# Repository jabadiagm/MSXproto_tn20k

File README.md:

# MSXproto_tn20k
Placa de prototipado para cartucho MSX y Tang Nano 20K

Placa de prototipo para conectar una Tang Nano 20K a una ranura de cartucho MSX. Se incluyen adaptadores de nivel de 5V a 3.3V para los pines de salida digitales del cartucho.

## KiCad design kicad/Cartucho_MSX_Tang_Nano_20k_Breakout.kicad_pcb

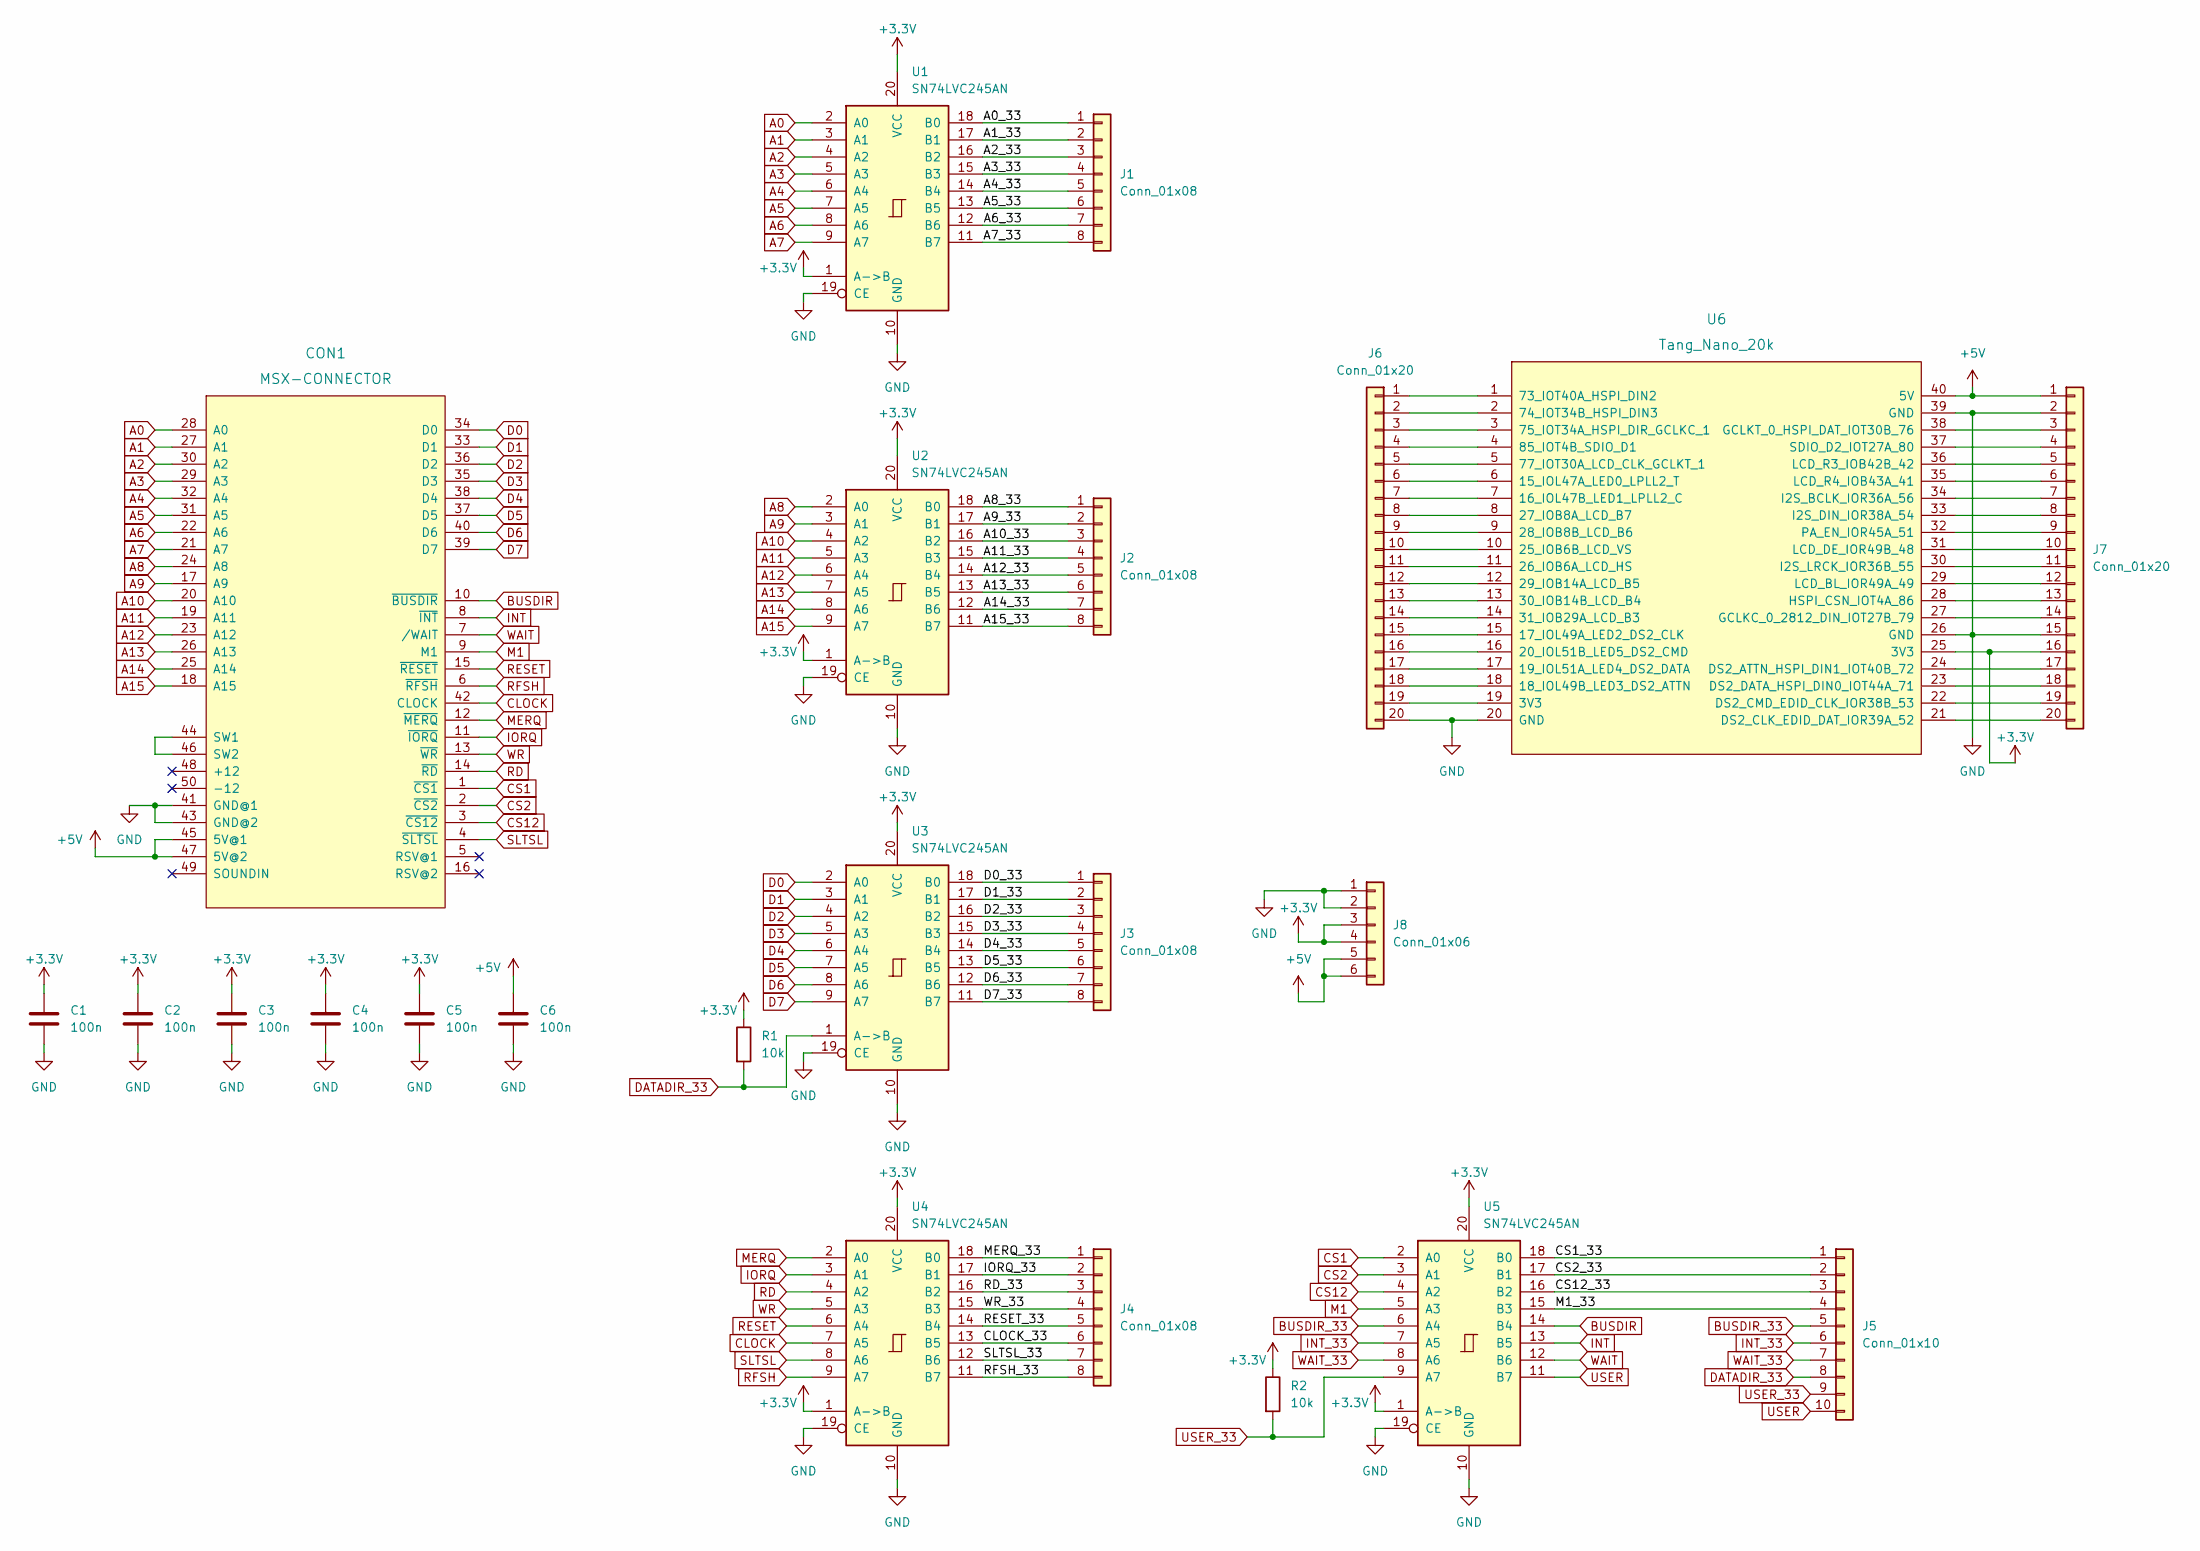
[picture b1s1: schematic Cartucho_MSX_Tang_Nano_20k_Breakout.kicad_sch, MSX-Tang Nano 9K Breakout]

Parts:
C1, C2, C3, C4, C5, C6: 100n; C_Disc_D4.3mm_W1.9mm_P5.00mm
CON1: MSX-CONNECTOR; CARTRIDGE_MSX_XL
J1, J2, J3, J4: Conn_01x08; PinSocket_1x08_P2.54mm_Vertical
J5: Conn_01x10; PinSocket_1x10_P2.54mm_Vertical
J6, J7: Conn_01x20; PinSocket_1x20_P2.54mm_Vertical
J8: Conn_01x06; PinSocket_1x06_P2.54mm_Vertical
R1, R2: 10k; R_Axial_DIN0207_L6.3mm_D2.5mm_P7.62mm_Horizontal
U1, U2, U3, U4, U5: SN74LVC245AN; DIP-20_W7.62mm
U6: Tang_Nano_20k

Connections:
/A0_33: J1.1, U1.18 (B0)
/A1_33: J1.2, U1.17 (B1)
/A2_33: J1.3, U1.16 (B2)
/A3_33: J1.4, U1.15 (B3)
/A4_33: J1.5, U1.14 (B4)
/A5_33: J1.6, U1.13 (B5)
/A6_33: J1.7, U1.12 (B6)
/A7_33: J1.8, U1.11 (B7)
/A8_33: J2.1, U2.18 (B0)
/A9_33: J2.2, U2.17 (B1)
/A10_33: J2.3, U2.16 (B2)
/A11_33: J2.4, U2.15 (B3)
/A12_33: J2.5, U2.14 (B4)
/A13_33: J2.6, U2.13 (B5)
/A14_33: J2.7, U2.12 (B6)
/A15_33: J2.8, U2.11 (B7)
/CLOCK_33: J4.6, U4.13 (B5)
/CS1_33: J5.1, U5.18 (B0)
/CS2_33: J5.2, U5.17 (B1)
/CS12_33: J5.3, U5.16 (B2)
/D0_33: J3.1, U3.18 (B0)
/D1_33: J3.2, U3.17 (B1)
/D2_33: J3.3, U3.16 (B2)
/D3_33: J3.4, U3.15 (B3)
/D4_33: J3.5, U3.14 (B4)
/D5_33: J3.6, U3.13 (B5)
/D6_33: J3.7, U3.12 (B6)
/D7_33: J3.8, U3.11 (B7)
/IORQ_33: J4.2, U4.17 (B1)
/M1_33: J5.4, U5.15 (B3)
/MERQ_33: J4.1, U4.18 (B0)
/RD_33: J4.3, U4.16 (B2)
/RESET_33: J4.5, U4.14 (B4)
/RFSH_33: J4.8, U4.11 (B7)
/SLTSL_33: J4.7, U4.12 (B6)
/WR_33: J4.4, U4.15 (B3)
A0: CON1.28 (A0), U1.2 (A0)
A1: CON1.27 (A1), U1.3 (A1)
A2: CON1.30 (A2), U1.4 (A2)
A3: CON1.29 (A3), U1.5 (A3)
A4: CON1.32 (A4), U1.6 (A4)
A5: CON1.31 (A5), U1.7 (A5)
A6: CON1.22 (A6), U1.8 (A6)
A7: CON1.21 (A7), U1.9 (A7)
A8: CON1.24 (A8), U2.2 (A0)
A9: CON1.17 (A9), U2.3 (A1)
A10: CON1.20 (A10), U2.4 (A2)
A11: CON1.19 (A11), U2.5 (A3)
A12: CON1.23 (A12), U2.6 (A4)
A13: CON1.26 (A13), U2.7 (A5)
A14: CON1.25 (A14), U2.8 (A6)
A15: CON1.18 (A15), U2.9 (A7)
BUSDIR: CON1.10 (~BUSDIR), U5.14 (B4)
BUSDIR_33: J5.5, U5.6 (A4)
CLOCK: CON1.42 (CLOCK), U4.7 (A5)
CS1: CON1.1 (~CS1), U5.2 (A0)
CS2: CON1.2 (~CS2), U5.3 (A1)
CS12: CON1.3 (~CS12), U5.4 (A2)
D0: CON1.34 (D0), U3.2 (A0)
D1: CON1.33 (D1), U3.3 (A1)
D2: CON1.36 (D2), U3.4 (A2)
D3: CON1.35 (D3), U3.5 (A3)
D4: CON1.38 (D4), U3.6 (A4)
D5: CON1.37 (D5), U3.7 (A5)
D6: CON1.40 (D6), U3.8 (A6)
D7: CON1.39 (D7), U3.9 (A7)
DATADIR_33: J5.8, R1.2, U3.1 (A->B)
INT: CON1.8 (~INT), U5.13 (B5)
INT_33: J5.6, U5.7 (A5)
IORQ: CON1.11 (~IORQ), U4.3 (A1)
M1: CON1.9 (M1), U5.5 (A3)
MERQ: CON1.12 (~MERQ), U4.2 (A0)
unnamed: CON1.44 (SW1), CON1.46 (SW2)
unnamed: J6.1, U6.1 (73_IOT40A_HSPI_DIN2)
unnamed: J6.2, U6.2 (74_IOT34B_HSPI_DIN3)
unnamed: J6.3, U6.3 (75_IOT34A_HSPI_DIR_GCLKC_1)
unnamed: J6.4, U6.4 (85_IOT4B_SDIO_D1)
unnamed: J6.5, U6.5 (77_IOT30A_LCD_CLK_GCLKT_1)
unnamed: J6.6, U6.6 (15_IOL47A_LED0_LPLL2_T)
unnamed: J6.7, U6.7 (16_IOL47B_LED1_LPLL2_C)
unnamed: J6.8, U6.8 (27_IOB8A_LCD_B7)
unnamed: J6.9, U6.9 (28_IOB8B_LCD_B6)
unnamed: J6.10, U6.10 (25_IOB6B_LCD_VS)
unnamed: J6.11, U6.11 (26_IOB6A_LCD_HS)
unnamed: J6.12, U6.12 (29_IOB14A_LCD_B5)
unnamed: J6.13, U6.13 (30_IOB14B_LCD_B4)
unnamed: J6.14, U6.14 (31_IOB29A_LCD_B3)
unnamed: J6.15, U6.15 (17_IOL49A_LED2_DS2_CLK)
unnamed: J6.16, U6.16 (20_IOL51B_LED5_DS2_CMD)
unnamed: J6.17, U6.17 (19_IOL51A_LED4_DS2_DATA)
unnamed: J6.18, U6.18 (18_IOL49B_LED3_DS2_ATTN)
unnamed: J6.19, U6.19 (3V3)
unnamed: J7.3, U6.38 (GCLKT_0_HSPI_DAT_IOT30B_76)
unnamed: J7.4, U6.37 (SDIO_D2_IOT27A_80)
unnamed: J7.5, U6.36 (LCD_R3_IOB42B_42)
unnamed: J7.6, U6.35 (LCD_R4_IOB43A_41)
unnamed: J7.7, U6.34 (I2S_BCLK_IOR36A_56)
unnamed: J7.8, U6.33 (I2S_DIN_IOR38A_54)
unnamed: J7.9, U6.32 (PA_EN_IOR45A_51)
unnamed: J7.10, U6.31 (LCD_DE_IOR49B_48)
unnamed: J7.11, U6.30 (I2S_LRCK_IOR36B_55)
unnamed: J7.12, U6.29 (LCD_BL_IOR49A_49)
unnamed: J7.13, U6.28 (HSPI_CSN_IOT4A_86)
unnamed: J7.14, U6.27 (GCLKC_0_2812_DIN_IOT27B_79)
unnamed: J7.17, U6.24 (DS2_ATTN_HSPI_DIN1_IOT40B_72)
unnamed: J7.18, U6.23 (DS2_DATA_HSPI_DIN0_IOT44A_71)
unnamed: J7.19, U6.22 (DS2_CMD_EDID_CLK_IOR38B_53)
unnamed: J7.20, U6.21 (DS2_CLK_EDID_DAT_IOR39A_52)
RD: CON1.14 (~RD), U4.4 (A2)
RESET: CON1.15 (~RESET), U4.6 (A4)
RFSH: CON1.6 (~RFSH), U4.9 (A7)
SLTSL: CON1.4 (~SLTSL), U4.8 (A6)
USER: J5.10, U5.11 (B7)
USER_33: J5.9, R2.2, U5.9 (A7)
WAIT: CON1.7 (/WAIT), U5.12 (B6)
WAIT_33: J5.7, U5.8 (A6)
WR: CON1.13 (~WR), U4.5 (A3)

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
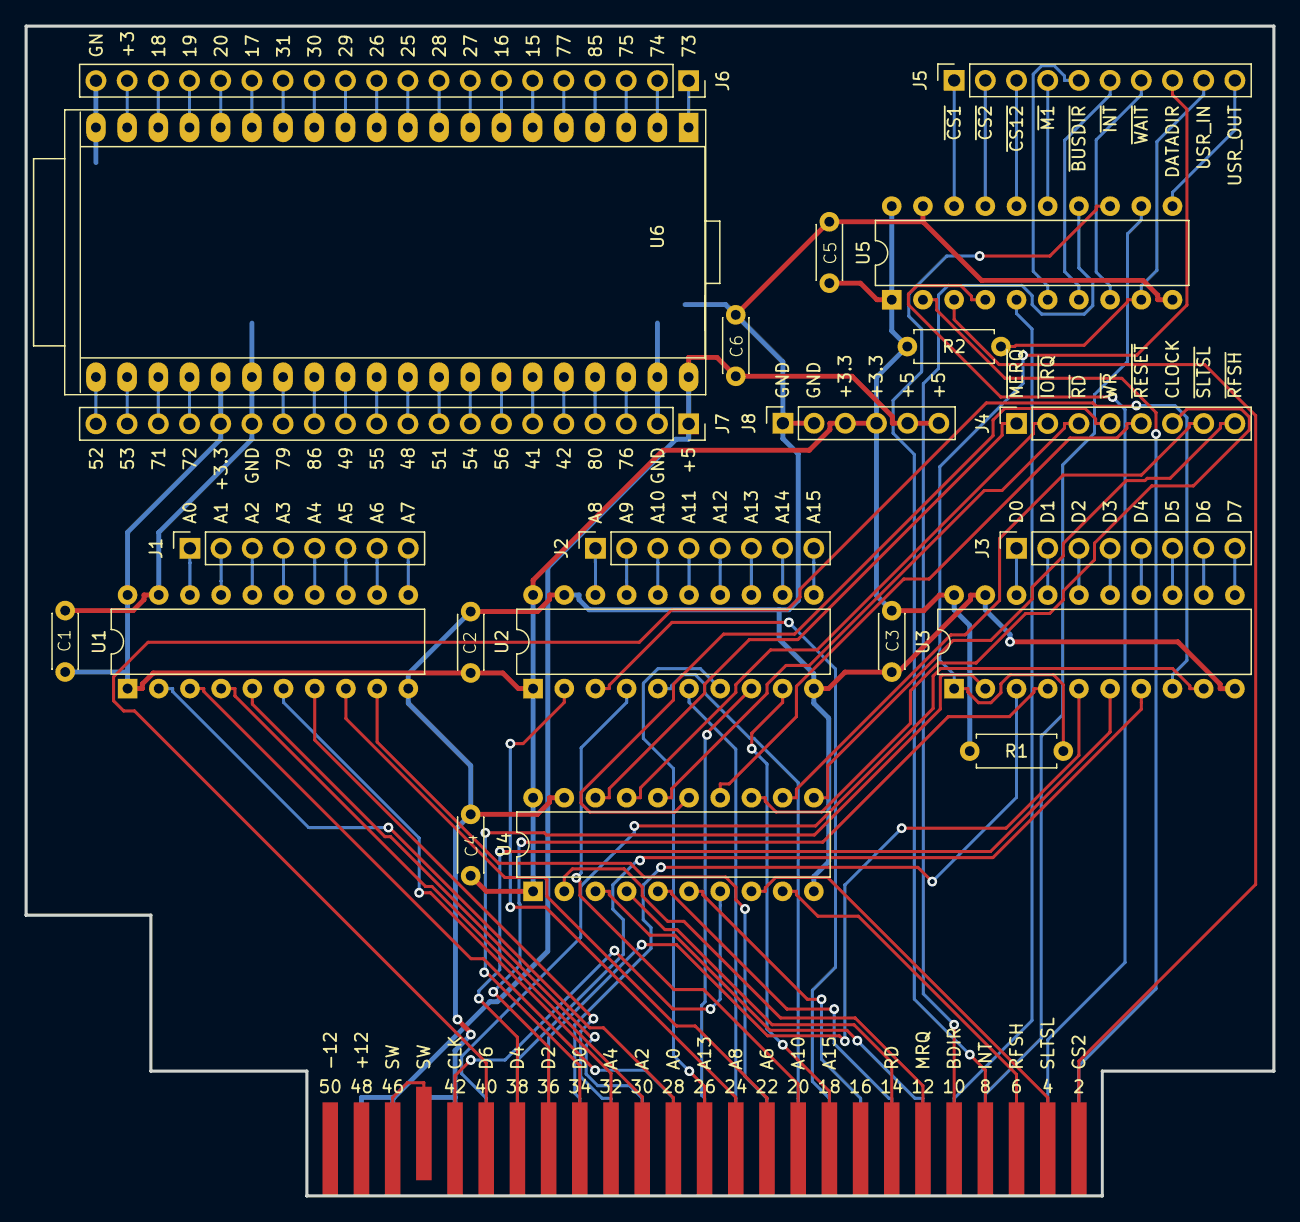
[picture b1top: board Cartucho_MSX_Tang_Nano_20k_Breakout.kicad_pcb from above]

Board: 2 copper layers, 101.6 x 95.2 mm, 23 parts (0 on the bottom side), 120 nets.

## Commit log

2023-08-14 Inicial
2023-08-14 Corregido nombre
